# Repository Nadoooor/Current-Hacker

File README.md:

# Current-Hacker
## PCB:

## Schematic:

## 3D Model:

## Description:
### This is my first PCB and my first use of Kicad. A PCB detects the current flowing in a wire using a coil and transistors. It is in the shape of a snake, and the coil is its tongue. It has two LEDs in its eyes that light up when it detects current, also it vibrates near its tail.
## My slack Username: Nadooor
# List of Materials:
### * 2 LEDs
### * 3 NPN 2N3904 transistors
### * 1 mini motor disc
### * 1 (1K ohm) resistor
### * 1 (330 ohm) resistor
### * 1 (1M ohm) resistor
### * 2 (1x02 connector Pins)
### * 1 Push Button

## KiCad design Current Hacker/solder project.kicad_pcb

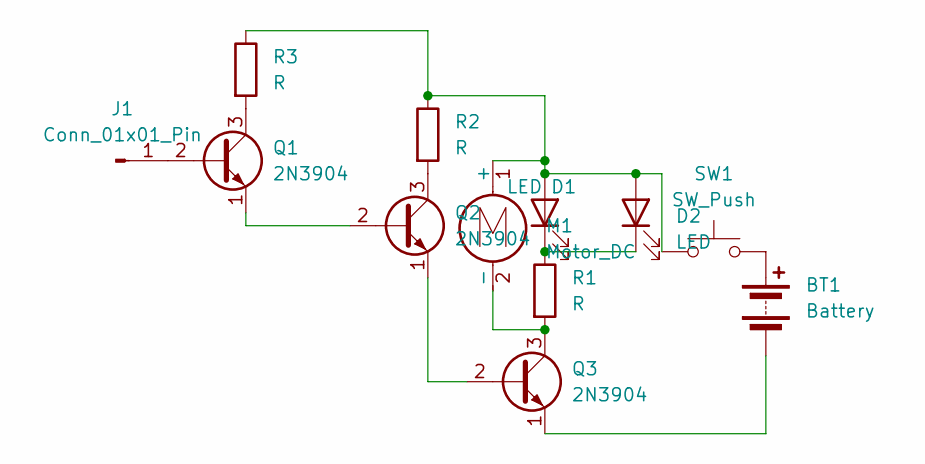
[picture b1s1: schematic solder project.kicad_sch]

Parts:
BT1: Battery; PinHeader_1x02_P2.54mm_Vertical
D1, D2: LED; LED_D5.0mm
J1: Conn_01x01_Pin; PinHeader_1x01_P2.54mm_Vertical
M1: Motor_DC; PinHeader_1x02_P2.54mm_Vertical
Q1, Q2, Q3: 2N3904; TO-92L_HandSolder
R1, R2, R3: R; R_Axial_DIN0207_L6.3mm_D2.5mm_P7.62mm_Horizontal
SW1: SW_Push; SW_PUSH_6mm

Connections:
unnamed: BT1.1 (+), SW1.2
unnamed: BT1.2 (-), Q3.1 (E)
unnamed: D1.2 (A), D2.2 (A), M1.1 (+), R2.1, R3.1, SW1.1
unnamed: D1.1 (K), D2.1 (K), R1.1
unnamed: J1.1, Q1.2 (B)
unnamed: M1.2 (-), Q3.3 (C), R1.2
unnamed: Q1.3 (C), R3.2
unnamed: Q1.1 (E), Q2.2 (B)
unnamed: Q2.3 (C), R2.2
unnamed: Q2.1 (E), Q3.2 (B)

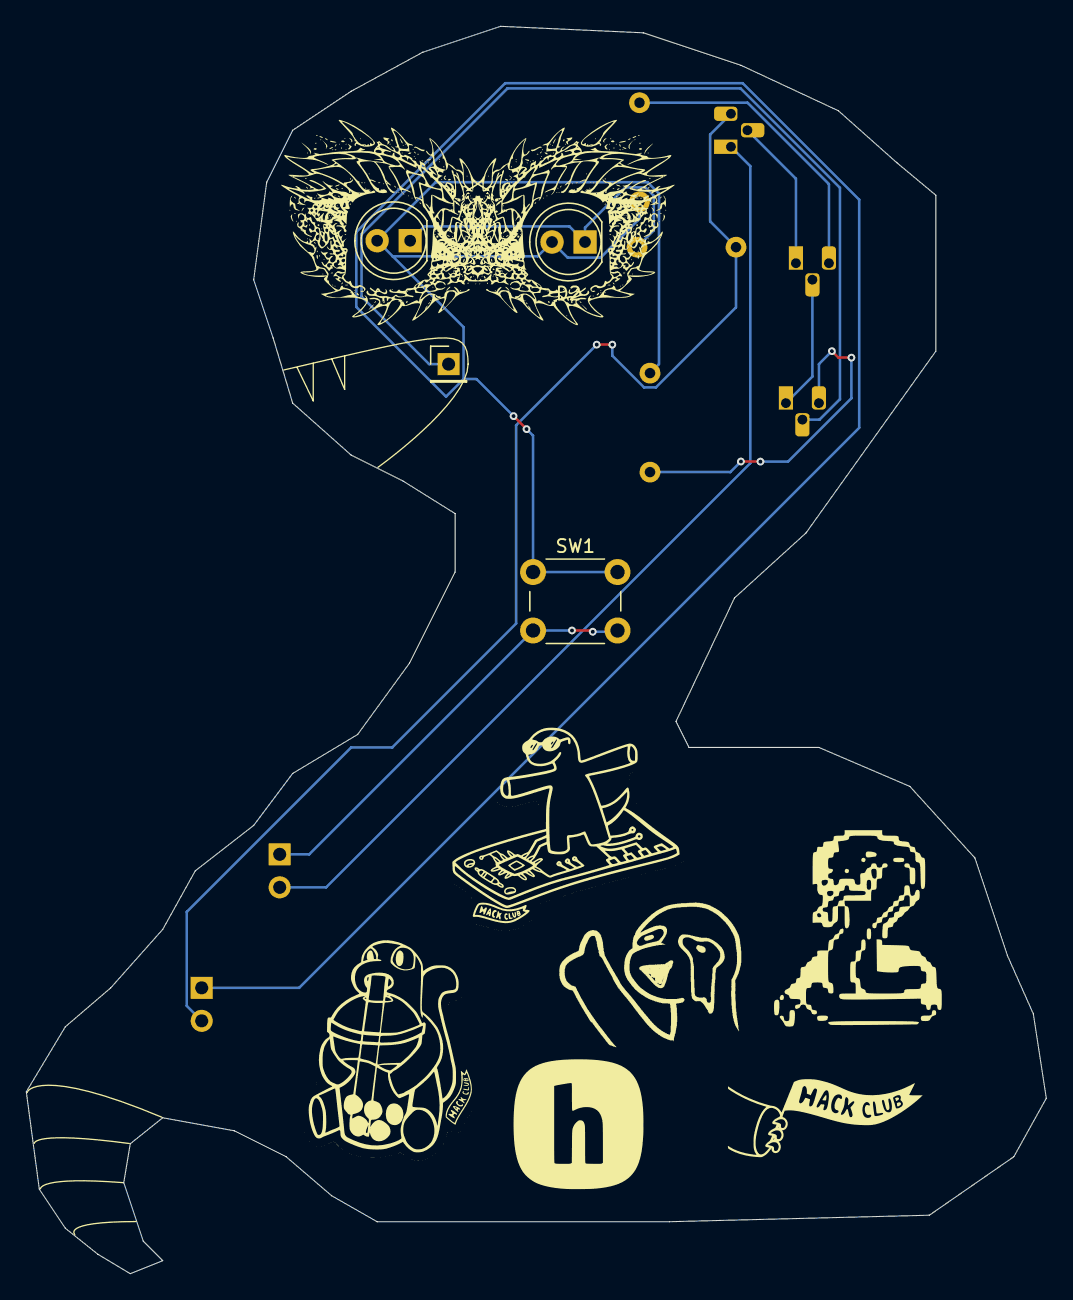
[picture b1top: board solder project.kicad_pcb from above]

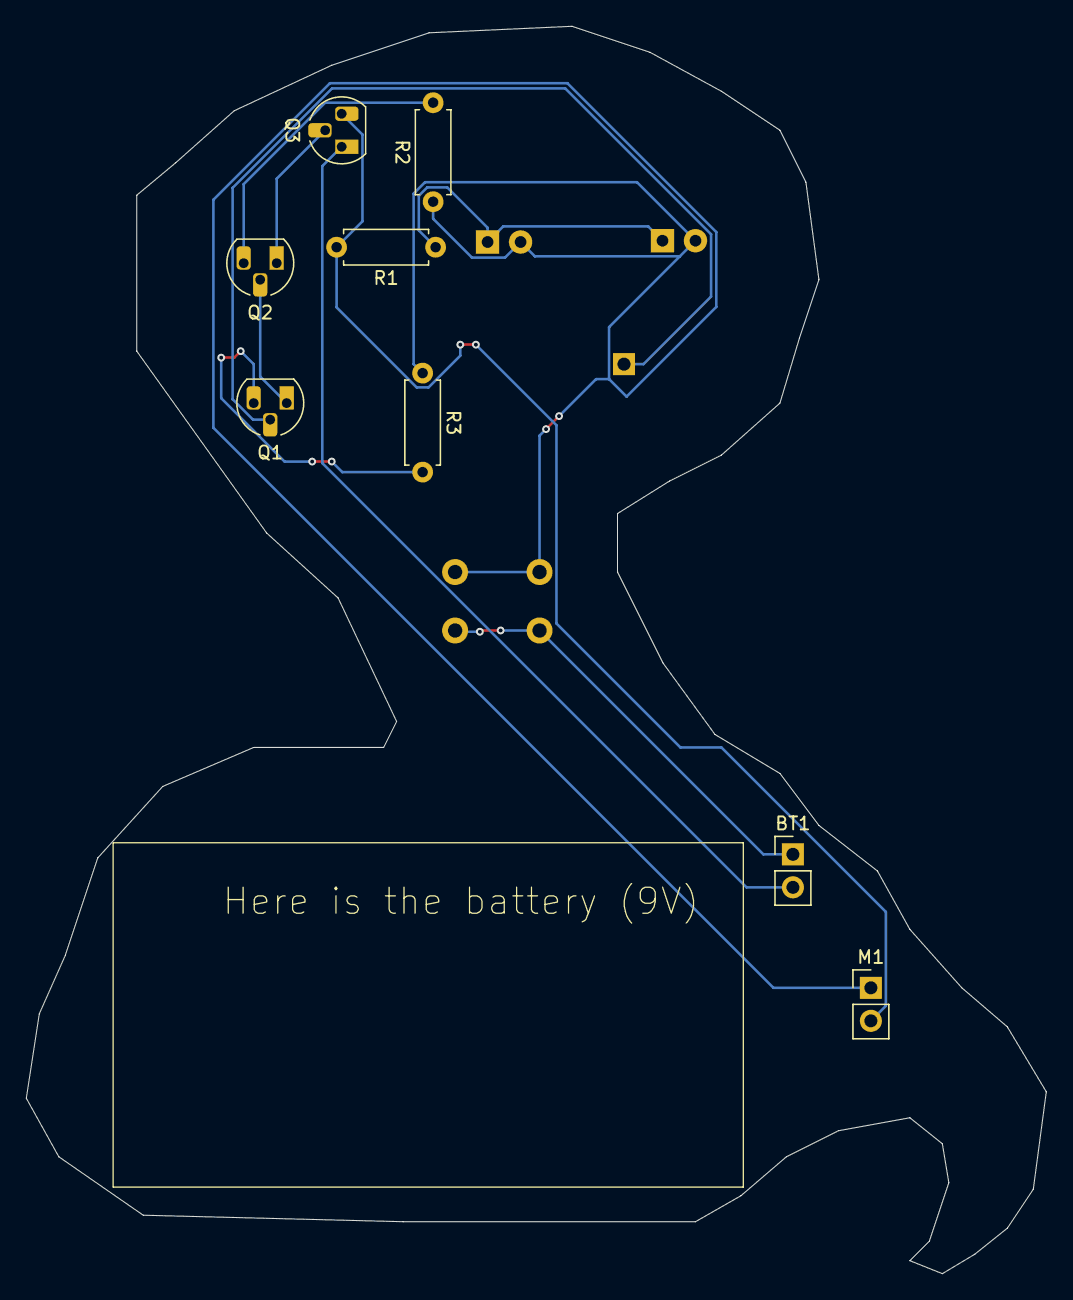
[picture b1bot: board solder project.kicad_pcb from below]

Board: 2 copper layers, 78.5 x 96.0 mm, 12 parts (8 on the bottom side), 10 nets.

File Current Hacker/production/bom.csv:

Designator,Footprint,Quantity,Value,LCSC Part #
BT1,PinHeader_1x02_P2.54mm_Vertical,1,Battery,
"D1, D2",LED_D5.0mm,2,LED,
J1,PinHeader_1x01_P2.54mm_Vertical,1,Conn_01x01_Pin,
M1,PinHeader_1x02_P2.54mm_Vertical,1,Motor_DC,
"Q1, Q2, Q3",TO-92L_HandSolder,3,2N3904,
"R1, R2, R3",R_Axial_DIN0207_L6.3mm_D2.5mm_P7.62mm_Horizontal,3,R,
SW1,SW_PUSH_6mm,1,SW_Push,

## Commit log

2025-04-30 Adding The Project's All files
2025-04-30 Rename solder_project.zip to The_Fabrication_File.zip
